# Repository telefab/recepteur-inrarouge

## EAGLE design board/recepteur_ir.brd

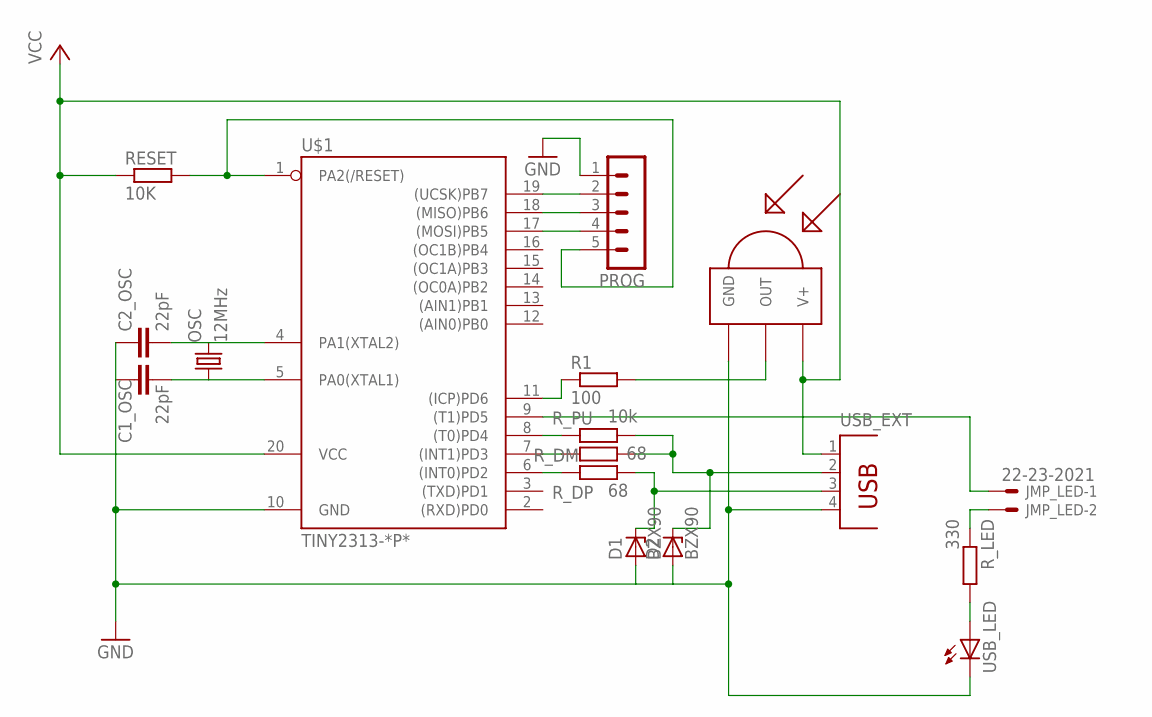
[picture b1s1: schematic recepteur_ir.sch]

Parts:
C1_OSC, C2_OSC: 22pF; C025-040X050
D1, D2: BZX90; DO34Z7
JMP_LED: 22-23-2021
OSC: 12MHz; HC49/S
PROG: MA05-1
R1: 100; 0204/7
RESET: 10K; 0204/7
R_DM: 68; 0204/7
R_DP: 68; 0204/7
R_LED: 330; 0204/7
R_PU: 10k; 0204/7
U$1: TINY2313-*P*; DIL20
U$2: TSOP2238; TSOP2XXX
USB_EXT: PN61729
USB_LED: LED3MM

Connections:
GND: C1_OSC.1, C2_OSC.1, D1.A, D2.A, PROG.1, U$1.10 (GND), U$2.GND, USB_EXT.4, USB_LED.K (C)
unnamed: C2_OSC.2, OSC.2, U$1.4 (PA1(XTAL2))
unnamed: C1_OSC.2, OSC.1, U$1.5 (PA0(XTAL1))
unnamed: R1.2, U$2.OUT
unnamed: PROG.5, RESET.2, U$1.1 (PA2(/RESET))
unnamed: D2.C, R_DM.2, R_PU.2, USB_EXT.2
unnamed: R_PU.1, U$1.8 ((T0)PD4)
unnamed: R_DM.1, U$1.7 ((INT1)PD3)
unnamed: R_DP.1, U$1.6 ((INT0)PD2)
unnamed: D1.C, R_DP.2, USB_EXT.3
unnamed: JMP_LED.1, U$1.9 ((T1)PD5)
unnamed: R_LED.2, USB_LED.A
unnamed: JMP_LED.2, R_LED.1
unnamed: PROG.2, U$1.19 ((UCSK)PB7)
unnamed: PROG.3, U$1.18 ((MISO)PB6)
unnamed: PROG.4, U$1.17 ((MOSI)PB5)
unnamed: R1.1, U$1.11 ((ICP)PD6)
VCC: RESET.1, U$1.20 (VCC), U$2.VCC (V+), USB_EXT.1

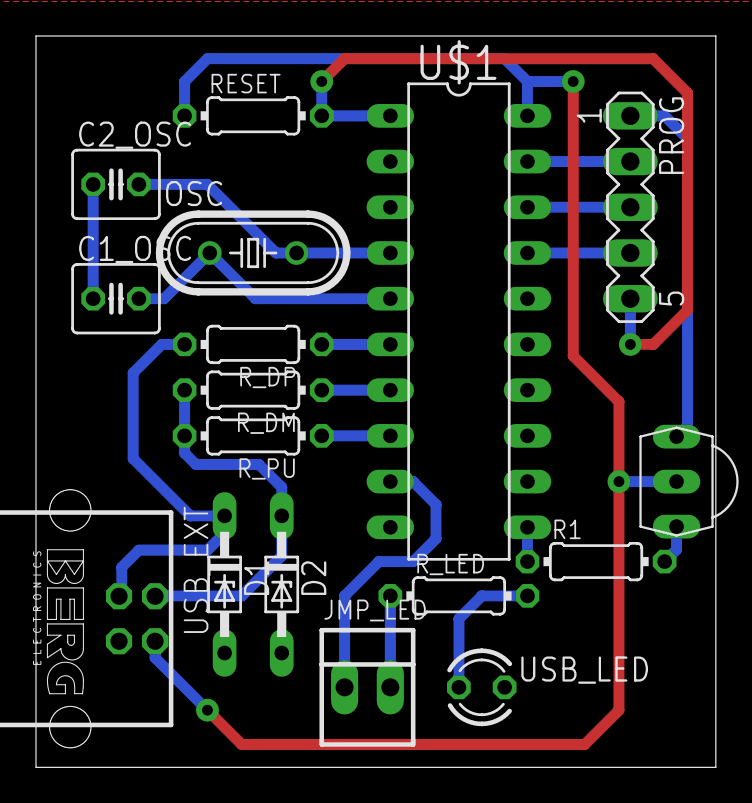
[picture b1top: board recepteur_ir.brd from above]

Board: 2 copper layers, 37.8 x 40.6 mm, 17 parts (0 on the bottom side), 18 nets.
